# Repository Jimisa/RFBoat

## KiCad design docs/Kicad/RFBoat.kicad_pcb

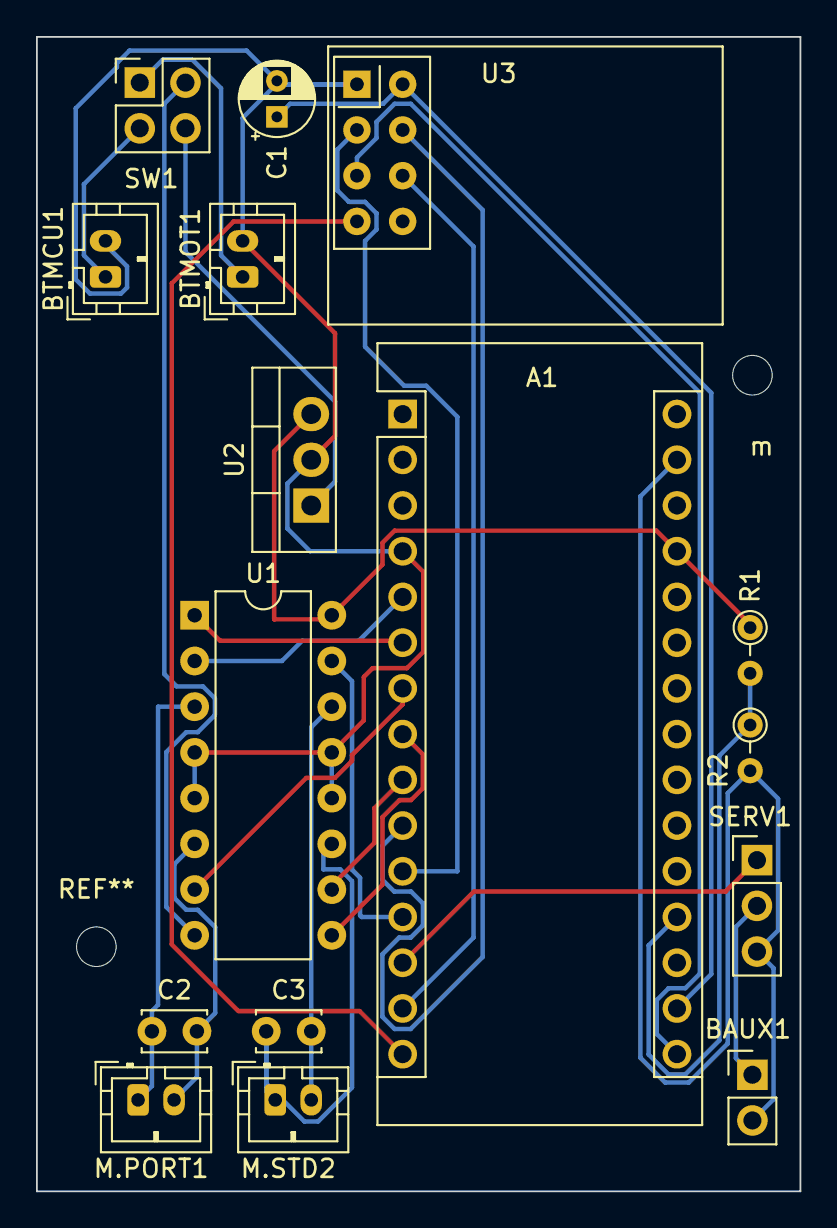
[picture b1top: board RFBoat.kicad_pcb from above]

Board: 2 copper layers, 42.4 x 64.1 mm, 17 parts (0 on the bottom side), 26 nets.

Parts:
A1: Arduino_Nano_v3.x; Arduino_Nano
BAUX1: Battery; PinHeader_1x02_P2.54mm_Vertical
BTMCU1: 2*AAA; JST_PH_B2B-PH-K_1x02_P2.00mm_Vertical
BTMOT1: 9V; JST_PH_B2B-PH-K_1x02_P2.00mm_Vertical
C1: 10µF; CP_Radial_D4.0mm_P2.00mm
C2, C3: C; C_Disc_D3.4mm_W2.1mm_P2.50mm
M.PORT1: Port; JST_PH_B2B-PH-K_1x02_P2.00mm_Vertical
M.STD2: Starboard; JST_PH_B2B-PH-K_1x02_P2.00mm_Vertical
R1: R_Photo; R_Axial_DIN0204_L3.6mm_D1.6mm_P2.54mm_Vertical
R2: R; R_Axial_DIN0204_L3.6mm_D1.6mm_P2.54mm_Vertical
SERV1: Motor_Servo; PinHeader_1x03_P2.54mm_Vertical
SW1: SW_DPST; PinHeader_2x02_P2.54mm_Vertical
U1: L293D; DIP-16_W7.62mm
U2: 5V regulator; TO-220-3_Vertical
U3: NRF24L01_Breakout; nRF24L01_Breakout
m: MountingHole_2.2mm_M2

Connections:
GND: A1.4 (GND), BTMCU1.2 (-), BTMOT1.2 (-), C1.2, U1.4 (GND), U1.5 (GND), U1.12 (GND), U1.13 (GND), U2.2 (GND), U3.1 (GND)
unnamed: A1.5 (D2), U1.2 (1A)
unnamed: A1.6 (D3), U1.1 (EN1,2)
unnamed: A1.7 (D4), U1.7 (2A)
unnamed: A1.8 (D5), U1.9 (EN3,4)
unnamed: A1.9 (D6), U1.10 (3A)
unnamed: A1.12 (D9), U1.15 (4A)
unnamed: A1.13 (D10), SERV1.1 (PWM)
unnamed: A1.14 (D11), U3.6 (MOSI)
unnamed: A1.15 (D12), U3.7 (MISO)
unnamed: A1.16 (D13), U3.5 (SCK)
unnamed: A1.17 (3V3), C1.1, U3.2 (VCC)
unnamed: A1.19 (A0), R1.2, R2.1
unnamed: A1.27 (+5V), R1.1, U1.16 (VCC1), U2.3 (VO)
unnamed: A1.29 (GND), BAUX1.2 (-), R2.2, SERV1.3 (-)
unnamed: BAUX1.1 (+), SERV1.2 (+)
unnamed: BTMCU1.1 (+), SW1.3
unnamed: BTMOT1.1 (+), SW1.1
unnamed: C2.1, M.PORT1.1 (+), U1.3 (1Y)
unnamed: C2.2, M.PORT1.2 (-), U1.6 (2Y)
unnamed: C3.1, M.STD2.1 (+), U1.11 (3Y)
unnamed: C3.2, M.STD2.2 (-), U1.14 (4Y)
unnamed: SW1.2, U1.8 (VCC2)
unnamed: SW1.4, U2.1 (VI)
unnamed: A1.11 (D8), U3.3 (CE)
unnamed: A1.10 (D7), U3.4 (~CSN)

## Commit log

2022-05-01 init with CE pin 10 and CSN pin 9
2022-05-01 add kicad schematics and pcb according ti init pinout
2022-05-02 changed pin layout to free last PWM pin (10) CE & CSN
2022-07-11 chanel lists configuration added code for RF test
2022-07-11 code for RF test
